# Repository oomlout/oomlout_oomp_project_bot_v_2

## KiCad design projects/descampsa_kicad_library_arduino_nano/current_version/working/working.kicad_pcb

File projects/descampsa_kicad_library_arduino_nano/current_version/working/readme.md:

# kicad_library
 
## summary 
* id: descampsa_kicad_library_arduino_nano
* user: descampsa
* name: kicad_library
* board: arduino_nano
* repo: https://github.com/descampsa/kicad-library
* src_file_repo_kicad_pcb: template/Arduino_Nano/Arduino_Nano.kicad_pcb
* src_file_repo_kicad_pcb_link: https://github.com/descampsa/kicad-library/tree/master/template/Arduino_Nano/Arduino_Nano.kicad_pcb

* src_file_repo_sch: template/Arduino_Nano/Arduino_Nano.sch
* src_file_repo_sch_link: https://github.com/descampsa/kicad-library/tree/master/template/Arduino_Nano/Arduino_Nano.sch
* full details link: https://github.com/oomlout/oomlout_oomp_project_bot_v_2/tree/main/projects/descampsa_kicad_library_arduino_nano/current_version/working

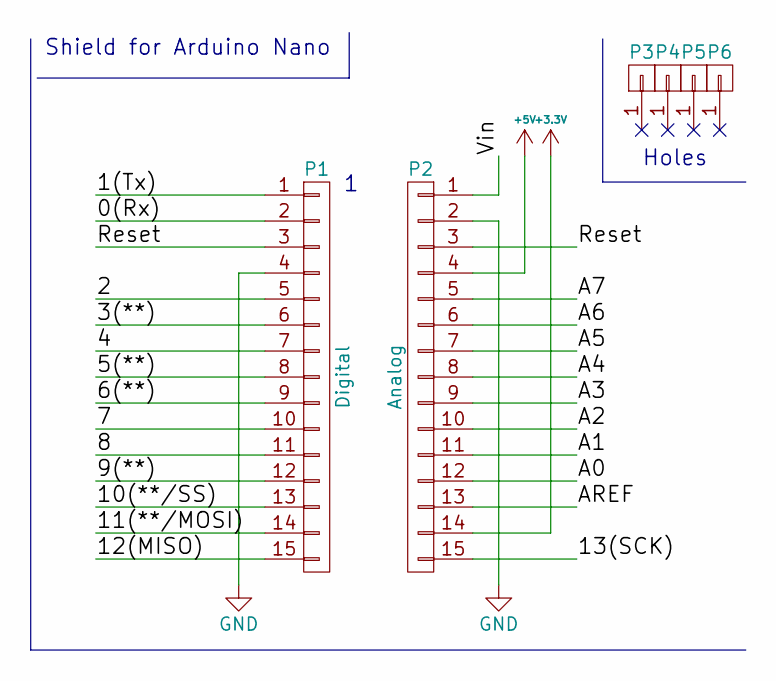
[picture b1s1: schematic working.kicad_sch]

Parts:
P1: Digital; Socket_Strip_Arduino_1x15
P2: Analog; Socket_Strip_Arduino_1x15
P3, P4, P5, P6: CONN_01X01; 1pin_Nano

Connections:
+3V3: P2.14
+5V: P2.4
/0(Rx): P1.2
/1(Tx): P1.1
/2: P1.5
/3(**): P1.6
/4: P1.7
/5(**): P1.8
/6(**): P1.9
/7: P1.10
/8: P1.11
/9(**): P1.12
/10(**/SS): P1.13
/11(**/MOSI): P1.14
/12(MISO): P1.15
/13(SCK): P2.15
/A0: P2.12
/A1: P2.11
/A2: P2.10
/A3: P2.9
/A4: P2.8
/A5: P2.7
/A6: P2.6
/A7: P2.5
/AREF: P2.13
/Reset: P1.3, P2.3
/Vin: P2.1
GND: P1.4, P2.2

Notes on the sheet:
Holes
Shield for Arduino Nano

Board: 2 copper layers, 6 parts (0 on the bottom side), 2 nets, no tracks yet.

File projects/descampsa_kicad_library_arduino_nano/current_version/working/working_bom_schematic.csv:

"Source:","C:\gh\oomlout_oomp_project_bot_v_2\projects\descampsa_kicad_library_arduino_nano\current_version\working\working.kicad_sch"
"Date:","01/10/2023 22:07:57"
"Tool:","Eeschema 7.0.6"
"Generator:","C:/Program Files/KiCad/7.0/bin/scripting/plugins/bom_csv_grouped_by_value_with_fp.py"
"Component Count:","6"
"Ref","Qnty","Value","Cmp name","Footprint","Description","Vendor","DNP"
"P1","1","Digital","CONN_01X15","Socket_Arduino_Nano:Socket_Strip_Arduino_1x15","","",""
"P2","1","Analog","CONN_01X15","Socket_Arduino_Nano:Socket_Strip_Arduino_1x15","","",""
"P3, P4, P5, P6","4","CONN_01X01","CONN_01X01","Socket_Arduino_Nano:1pin_Nano","","",""

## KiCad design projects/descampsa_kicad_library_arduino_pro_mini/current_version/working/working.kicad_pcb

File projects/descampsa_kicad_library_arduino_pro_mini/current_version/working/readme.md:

# kicad_library
 
## summary 
* id: descampsa_kicad_library_arduino_pro_mini
* user: descampsa
* name: kicad_library
* board: arduino_pro_mini
* repo: https://github.com/descampsa/kicad-library
* src_file_repo_kicad_pcb: template/Arduino_Pro_Mini/Arduino_Pro_Mini.kicad_pcb
* src_file_repo_kicad_pcb_link: https://github.com/descampsa/kicad-library/tree/master/template/Arduino_Pro_Mini/Arduino_Pro_Mini.kicad_pcb

* src_file_repo_sch: template/Arduino_Pro_Mini/Arduino_Pro_Mini.sch
* src_file_repo_sch_link: https://github.com/descampsa/kicad-library/tree/master/template/Arduino_Pro_Mini/Arduino_Pro_Mini.sch
* full details link: https://github.com/oomlout/oomlout_oomp_project_bot_v_2/tree/main/projects/descampsa_kicad_library_arduino_pro_mini/current_version/working

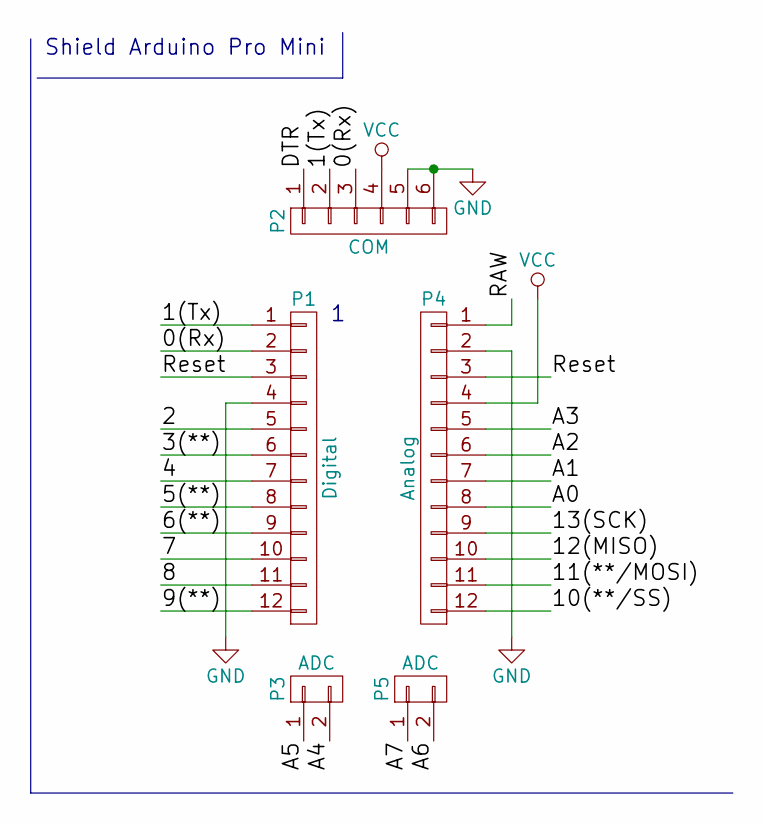
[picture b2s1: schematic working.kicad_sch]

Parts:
P1: Digital; Socket_Strip_Arduino_1x12
P2: COM; Socket_Strip_Arduino_1x06
P3, P5: ADC; Socket_Strip_Arduino_1x02
P4: Analog; Socket_Strip_Arduino_1x12

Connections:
/0(Rx): P1.2, P2.3
/1(Tx): P1.1, P2.2
/2: P1.5
/3(**): P1.6
/4: P1.7
/5(**): P1.8
/6(**): P1.9
/7: P1.10
/8: P1.11
/9(**): P1.12
/10(**/SS): P4.12
/11(**/MOSI): P4.11
/12(MISO): P4.10
/13(SCK): P4.9
/A0: P4.8
/A1: P4.7
/A2: P4.6
/A3: P4.5
/A4: P3.2
/A5: P3.1
/A6: P5.2
/A7: P5.1
/DTR: P2.1
/RAW: P4.1
/Reset: P1.3, P4.3
GND: P1.4, P2.5, P2.6, P4.2
VCC: P2.4, P4.4

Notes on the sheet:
Shield Arduino Pro Mini

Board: 2 copper layers, 5 parts (0 on the bottom side), 5 nets, no tracks yet.

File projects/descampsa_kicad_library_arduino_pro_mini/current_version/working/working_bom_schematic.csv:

"Source:","C:\gh\oomlout_oomp_project_bot_v_2\projects\descampsa_kicad_library_arduino_pro_mini\current_version\working\working.kicad_sch"
"Date:","01/10/2023 22:23:47"
"Tool:","Eeschema 7.0.6"
"Generator:","C:/Program Files/KiCad/7.0/bin/scripting/plugins/bom_csv_grouped_by_value_with_fp.py"
"Component Count:","5"
"Ref","Qnty","Value","Cmp name","Footprint","Description","Vendor","DNP"
"P1","1","Digital","CONN_01X12","Socket_Arduino_Pro_Mini:Socket_Strip_Arduino_1x12","","",""
"P2","1","COM","CONN_01X06","Socket_Arduino_Pro_Mini:Socket_Strip_Arduino_1x06","","",""
"P3, P5","2","ADC","CONN_01X02","Socket_Arduino_Pro_Mini:Socket_Strip_Arduino_1x02","","",""
"P4","1","Analog","CONN_01X12","Socket_Arduino_Pro_Mini:Socket_Strip_Arduino_1x12","","",""

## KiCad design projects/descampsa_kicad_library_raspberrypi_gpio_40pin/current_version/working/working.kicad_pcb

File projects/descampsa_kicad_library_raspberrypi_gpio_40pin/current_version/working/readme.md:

# kicad_library
 
## summary 
* id: descampsa_kicad_library_raspberrypi_gpio_40pin
* user: descampsa
* name: kicad_library
* board: raspberrypi_gpio_40pin
* repo: https://github.com/descampsa/kicad-library
* src_file_repo_kicad_pcb: template/raspberrypi-gpio-40pin/raspberrypi-gpio-40pin.kicad_pcb
* src_file_repo_kicad_pcb_link: https://github.com/descampsa/kicad-library/tree/master/template/raspberrypi-gpio-40pin/raspberrypi-gpio-40pin.kicad_pcb

* src_file_repo_sch: template/raspberrypi-gpio-40pin/raspberrypi-gpio-40pin.sch
* src_file_repo_sch_link: https://github.com/descampsa/kicad-library/tree/master/template/raspberrypi-gpio-40pin/raspberrypi-gpio-40pin.sch
* full details link: https://github.com/oomlout/oomlout_oomp_project_bot_v_2/tree/main/projects/descampsa_kicad_library_raspberrypi_gpio_40pin/current_version/working

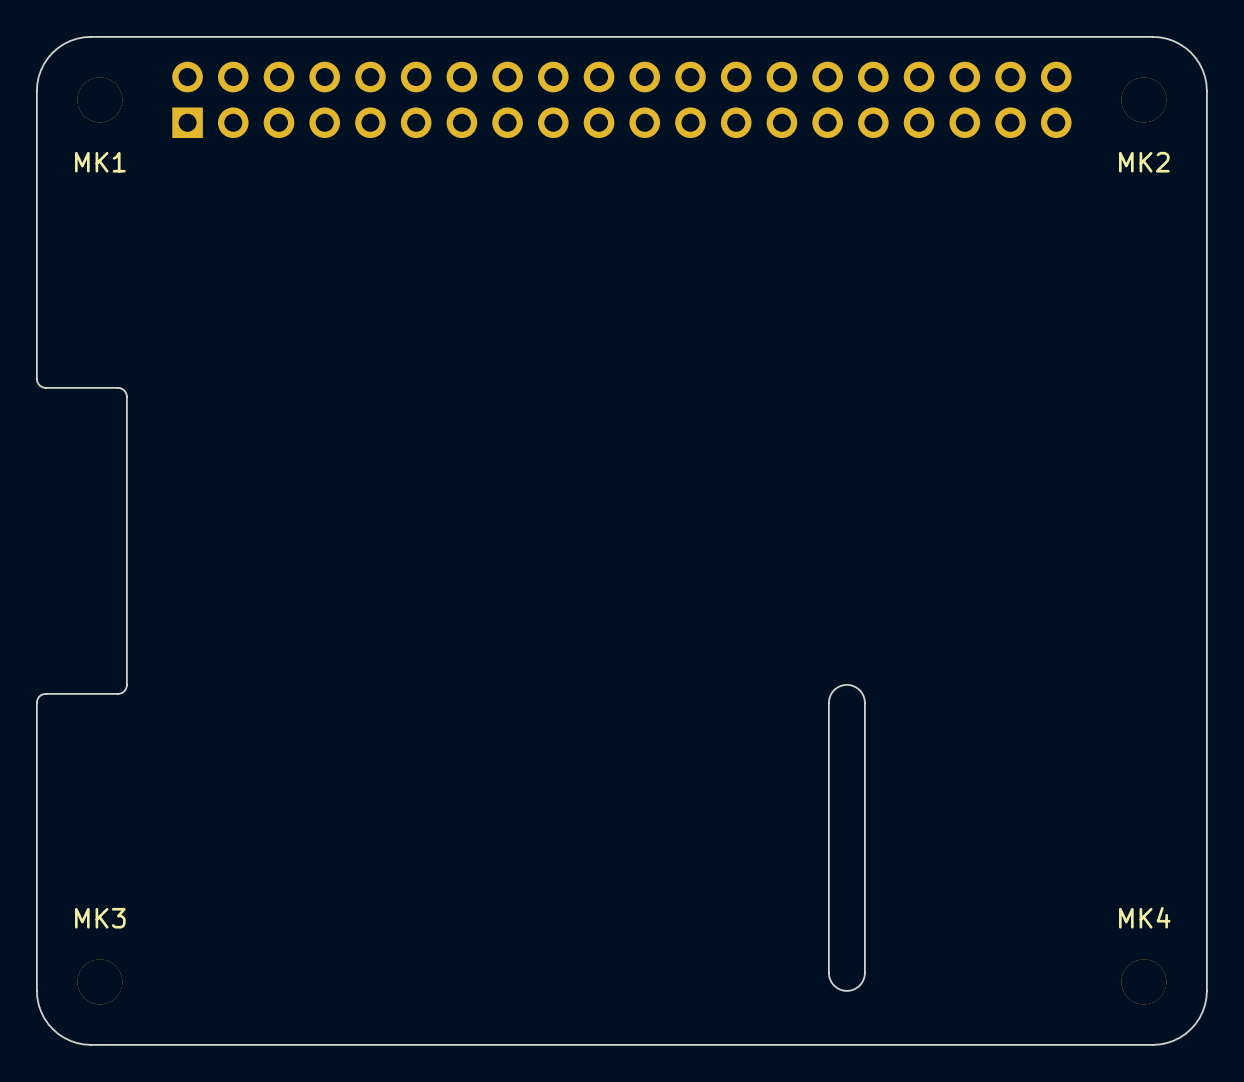
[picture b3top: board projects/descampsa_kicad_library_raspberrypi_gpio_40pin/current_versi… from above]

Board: 2 copper layers, 65.0 x 56.0 mm, 5 parts (1 on the bottom side), 3 nets, no tracks yet.

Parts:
MK1, MK2, MK3, MK4: M2.5; MountingHole_2-5mm
P1: Conn_02x20_Odd_Even; Socket_Strip_Straight_2x20_Pitch2.54mm

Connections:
+3V3: P1.1, P1.17
+5V: P1.2, P1.4
GND: P1.6, P1.9, P1.14, P1.20, P1.25, P1.30, P1.34, P1.39

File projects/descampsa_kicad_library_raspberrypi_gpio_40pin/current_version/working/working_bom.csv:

"Id";"Designator";"Footprint";"Quantity";"Designation";"Supplier and ref";
1;"MK1,MK2,MK3,MK4";"MountingHole_2-5mm";4;"M2.5";;;
2;"P1";"Socket_Strip_Straight_2x20_Pitch2.54mm";1;"Conn_02x20_Odd_Even";;;

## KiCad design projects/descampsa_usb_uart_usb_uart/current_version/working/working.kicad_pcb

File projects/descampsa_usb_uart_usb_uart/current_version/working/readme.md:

# usb_uart
 
## summary 
* id: descampsa_usb_uart_usb_uart
* user: descampsa
* name: usb_uart
* board: usb_uart
* repo: https://github.com/descampsa/usb_uart
* src_file_repo_kicad_pcb: v3/usb_uart.kicad_pcb
* src_file_repo_kicad_pcb_link: https://github.com/descampsa/usb_uart/tree/master/v3/usb_uart.kicad_pcb

* src_file_repo_sch: v3/usb_uart.sch
* src_file_repo_sch_link: https://github.com/descampsa/usb_uart/tree/master/v3/usb_uart.sch
* full details link: https://github.com/oomlout/oomlout_oomp_project_bot_v_2/tree/main/projects/descampsa_usb_uart_usb_uart/current_version/working

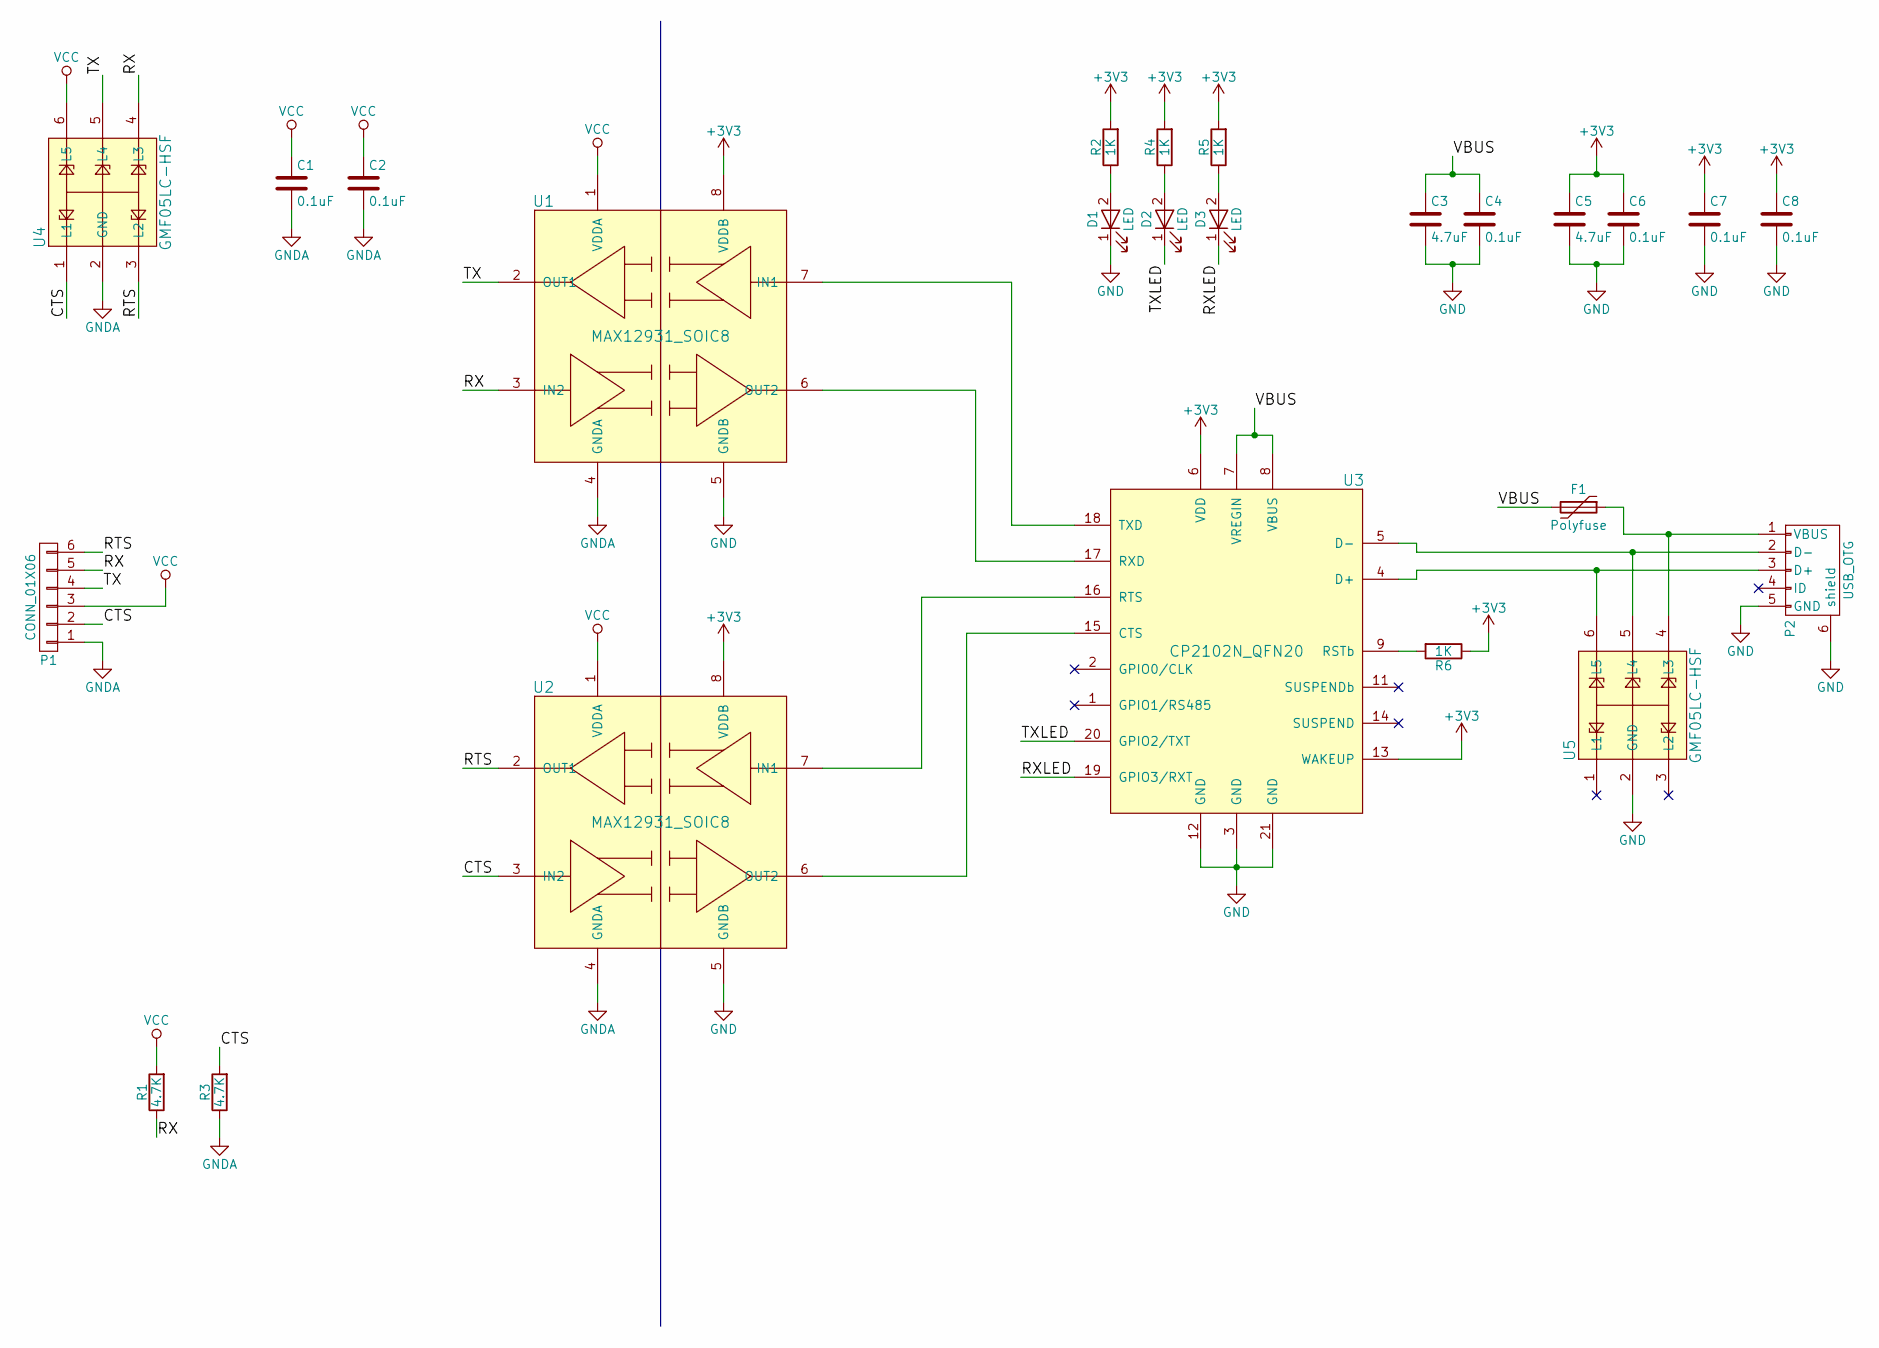
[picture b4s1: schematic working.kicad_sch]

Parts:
C1, C2, C4, C6, C7, C8: 0.1uF; C_0603
C3, C5: 4.7uF; C_0603
D1, D2, D3: LED; LED_0603
F1: Polyfuse; fuse_1206
P1: CONN_01X06; Pin_Header_Angled_1x06_Pitch2.54mm
P2: USB_OTG; ZX62D-B-5PA8
R1, R3: 4.7K; R_0603
R2, R4, R5, R6: 1K; R_0603
U1, U2: MAX12931_SOIC8; SOIC-8_3.9x4.9mm_Pitch1.27mm
U3: CP2102N_QFN20; QFN-20-1EP_3x3mm_Pitch0.5mm
U4, U5: GMF05LC-HSF; LLP75-6L

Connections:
+3V3: C5.1, C6.1, C7.1, C8.1, R2.2, R4.2, R5.2, R6.1, U1.8 (VDDB), U2.8 (VDDB), U3.6 (VDD), U3.13 (WAKEUP)
/CTS: P1.2, R3.2, U2.3 (IN2), U4.1 (L1)
/RTS: P1.6, U2.2 (OUT1), U4.3 (L2)
/RX: P1.5, R1.1, U1.3 (IN2), U4.4 (L3)
/RXLED: D3.1 (K), U3.19 (GPIO3/RXT)
/TX: P1.4, U1.2 (OUT1), U4.5 (L4)
/TXLED: D2.1 (K), U3.20 (GPIO2/TXT)
/VBUS: C3.1, C4.1, F1.2, U3.7 (VREGIN), U3.8 (VBUS)
GND: C3.2, C4.2, C5.2, C6.2, C7.2, C8.2, D1.1 (K), P2.5 (GND), P2.6 (shield), U1.5 (GNDB), U2.5 (GNDB), U3.3 (GND), U3.12 (GND), U3.21 (GND), U5.2 (GND)
GNDA: C1.2, C2.2, P1.1, R3.1, U1.4 (GNDA), U2.4 (GNDA), U4.2 (GND)
unnamed: D1.2 (A), R2.1
unnamed: D2.2 (A), R4.1
unnamed: D3.2 (A), R5.1
unnamed: F1.1, P2.1 (VBUS), U5.4 (L3)
unnamed: P2.2 (D-), U3.5 (D-), U5.5 (L4)
unnamed: P2.3 (D+), U3.4 (D+), U5.6 (L5)
unnamed: R6.2, U3.9 (RSTb)
unnamed: U1.6 (OUT2), U3.17 (RXD)
unnamed: U1.7 (IN1), U3.18 (TXD)
unnamed: U2.6 (OUT2), U3.15 (CTS)
unnamed: U2.7 (IN1), U3.16 (RTS)
VCC: C1.1, C2.1, P1.3, R1.2, U1.1 (VDDA), U2.1 (VDDA), U4.6 (L5)

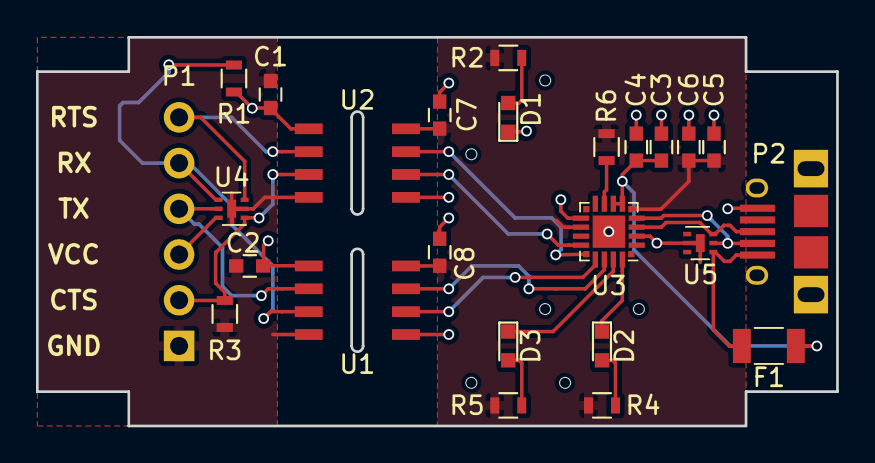
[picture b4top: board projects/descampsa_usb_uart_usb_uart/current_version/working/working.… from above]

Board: 2 copper layers, 44.5 x 21.6 mm, 25 parts (0 on the bottom side), 22 nets.

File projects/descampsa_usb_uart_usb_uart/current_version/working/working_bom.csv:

"Id";"Designator";"Footprint";"Quantity";"Designation";"Supplier and ref";
1;"C1,C2,C4,C6,C7,C8";"C_0603";6;"0.1uF";;;
2;"C3,C5";"C_0603";2;"4.7uF";;;
3;"P1";"Pin_Header_Angled_1x06_Pitch2.54mm";1;"CONN_01X06";;;
4;"P2";"ZX62D-B-5PA8";1;"USB_OTG";;;
5;"R1,R3";"R_0603";2;"4.7K";;;
6;"R2,R4,R5,R6";"R_0603";4;"1K";;;
7;"U1,U2";"SOIC-8_3.9x4.9mm_Pitch1.27mm";2;"MAX12931_SOIC8";;;
8;"U3";"QFN-20-1EP_3x3mm_Pitch0.5mm";1;"CP2102N_QFN20";;;
9;"REF**,REF**,REF**";"VLP";3;"VLP";;;
10;"D1,D2,D3";"LED_0603";3;"LED";;;
11;"F1";"fuse_1206";1;"Polyfuse";;;
12;"U4,U5";"LLP75-6L";2;"GMF05LC-HSF";;;
